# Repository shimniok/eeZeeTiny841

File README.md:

eeZeeTiny841 is a breakout / target board for breadboarding with the powerful ATtiny841.

[Click here for the User Guide](documentation/README.md)

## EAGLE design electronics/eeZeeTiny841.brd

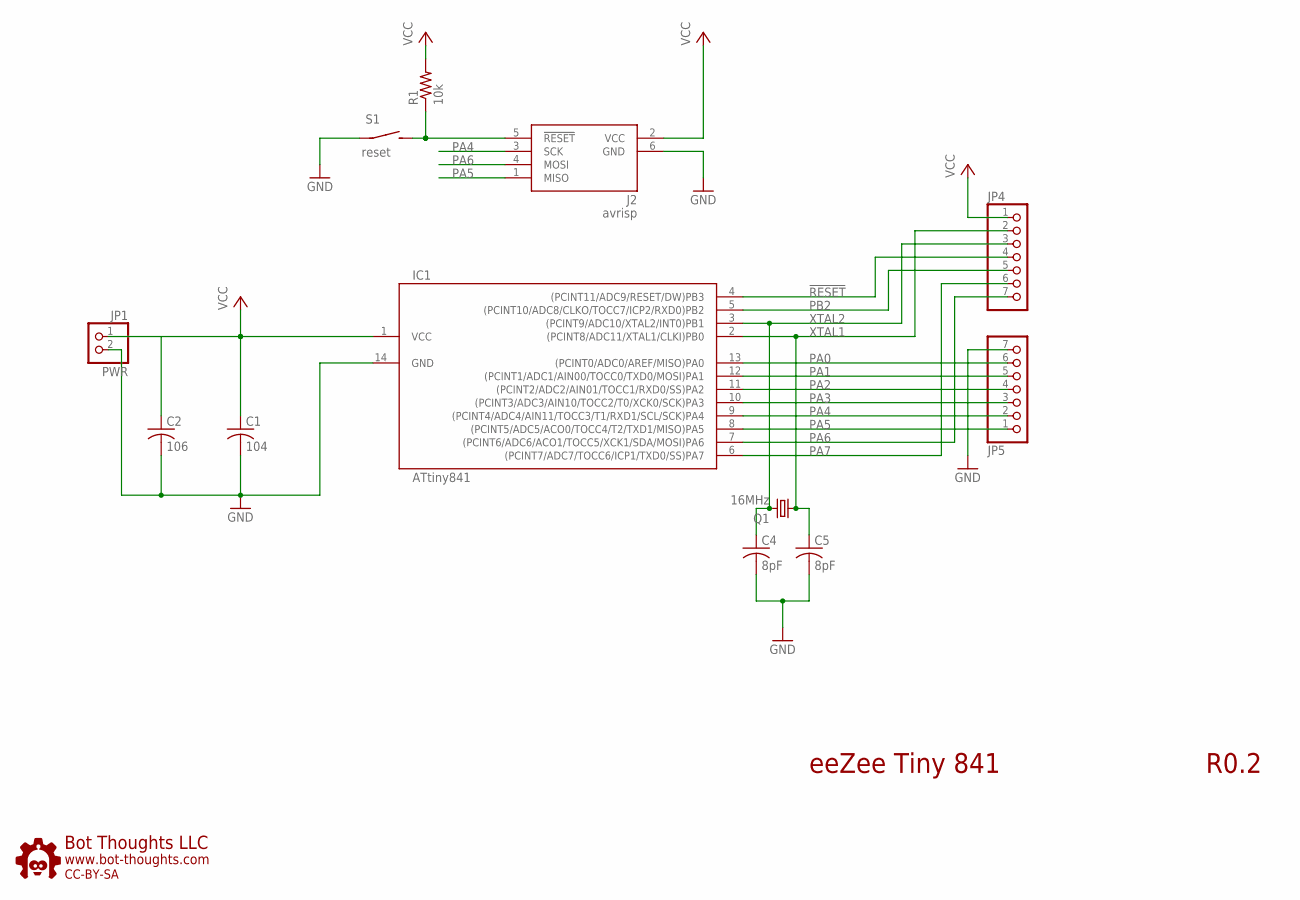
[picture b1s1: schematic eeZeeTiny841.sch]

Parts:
C1: 104; C0603; PARTNO 0603YC104KAT2A
C2: 106; C1206; PARTNO MCTT21X106M6R3CT
C4, C5: 8pF; C0603; PARTNO 0603YC104KAT2A
IC1: ATtiny841; 14SOICN
J2: avrisp; CON6P2R
JP1: PWR; 1X02-S
JP4, JP5: PINHD-1X07_2.54-S; 1X07-S
Q1: 16MHz; NDK_2PAD_5X3
R1: 10k; R0603; PARTNO ERJ-3GEYJ103V
S1: reset; 6MMTACTILE_RECT
U$1: BTLOGO-LOGO-MD; BTLOGOM

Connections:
!RESET: IC1.4 ((PCINT11/ADC9/RESET/DW)PB3), J2.5 (!RESET), JP4.4, R1.1, S1.P$2 (S)
GND: C1.2, C2.2, C4.2, C5.2, IC1.14 (GND), J2.6 (GND), JP1.2, JP5.7, S1.P$1
PA0: IC1.13 ((PCINT0/ADC0/AREF/MISO)PA0), JP5.6
PA1: IC1.12 ((PCINT1/ADC1/AIN00/TOCC0/TXD0/MOSI)PA1), JP5.5
PA2: IC1.11 ((PCINT2/ADC2/AIN01/TOCC1/RXD0/SS)PA2), JP5.4
PA3: IC1.10 ((PCINT3/ADC3/AIN10/TOCC2/T0/XCK0/SCK)PA3), JP5.3
PA4: IC1.9 ((PCINT4/ADC4/AIN11/TOCC3/T1/RXD1/SCL/SC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), J2.3 (SCK), JP5.2
PA5: IC1.8 ((PCINT5/ADC5/ACO0/TOCC4/T2/TXD1/MISO)PA5), J2.1 (MISO), JP5.1
PA6: IC1.7 ((PCINT6/ADC6/ACO1/TOCC5/XCK1/SDA/MOSI)P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), J2.4 (MOSI), JP4.7
PA7: IC1.6 ((PCINT7/ADC7/TOCC6/ICP1/TXD0/SS)PA7), JP4.6
PB2: IC1.5 ((PCINT10/ADC8/CLKO/TOCC7/ICP2/RXD0)PB2), JP4.5
VCC: C1.1, C2.1, IC1.1 (VCC), J2.2 (VCC), JP1.1, JP4.1, R1.2
XTAL1: C5.1, IC1.2 ((PCINT8/ADC11/XTAL1/CLKI)PB0), JP4.2, Q1.P$1 (1)
XTAL2: C4.1, IC1.3 ((PCINT9/ADC10/XTAL2/INT0)PB1), JP4.3, Q1.P$2 (2)

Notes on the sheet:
eeZee Tiny 841
R0.2

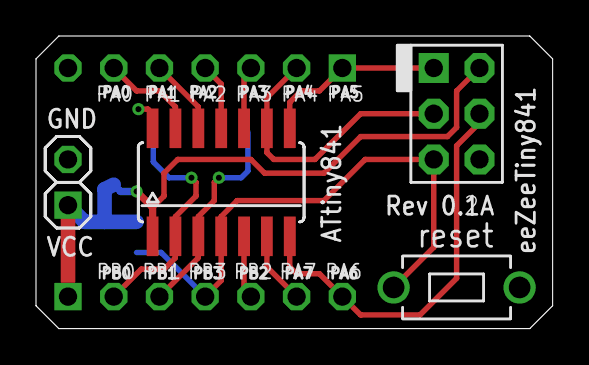
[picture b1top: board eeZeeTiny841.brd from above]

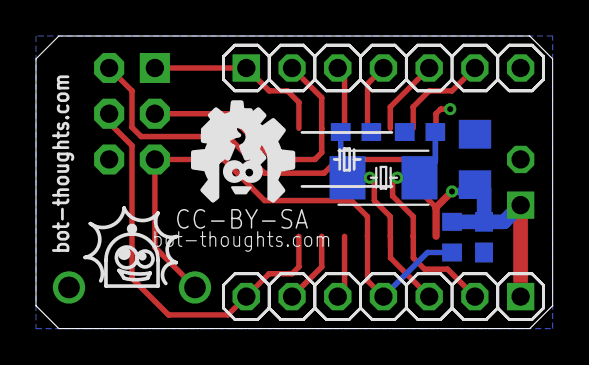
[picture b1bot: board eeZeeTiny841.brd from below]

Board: 2 copper layers, 28.7 x 16.3 mm, 13 parts (9 on the bottom side), 14 nets.

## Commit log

2014-01-22 Initial draft revision 0.1
2014-01-22 Fixing accidentally flipped schematic. D'oye!
2014-03-01 Example code for ATtiny841
2014-03-01 Minor mods to board/schematic. avrdude config from AVRfreaks forum.
2014-03-01 Renamed avrdude config
2014-03-01 Revised to use non-reset, non-xtal pins.
2014-03-01 Revised hierarchy with electronics subdir
2014-03-18 Subdirectory for multiple firmware examples
2014-03-18 Initial version, larson scanner type demo
2014-03-18 Fixed char / addition / subtraction bug, converted to larson type scanning, back and forth.
2014-03-18 Added hex files for easier testing
2014-10-17 Converted to 10mil/8mil spacing, changed PTHs to octagon.
2014-11-26 Added avrdude.conf content for ATtiny841, added README explaining how to set up.Z
2014-11-26 Modified readme to point to web-based help.
2015-04-24 Added delay in hopes of AVR Dragon having time to reset after install, fixed minor typos
2015-04-24 minor reformat. fixed loop variables. changed delay
2015-04-24 removed hex file
2015-05-01 added Makefile to larson scanner code
2015-05-05 Added LICENSE and README files
2015-06-10 Added wiki page in documentation
2015-06-10 renamed main wiki to README.md
2015-09-04 Formatting on Makefile
2015-11-17 Updated to current user guie format. Included additional soldering pics and instructions. Converted some images to local.
2015-11-17 Added local images
2015-11-17 removed unnecessary avrisp pinout
2015-11-17 renamed firmware to examples
2015-11-17 Added more local images, removed links to source, etc.
2015-11-17 removed hex link
2015-11-18 added assembly pictures
2016-02-11 fixed makefile fuse formatting, provided option for external clock
2016-02-11 fixed problem with comment on LFUSE
2016-02-12 reverted to internal 8mhz
2016-02-12 added fuses, minor reformatting
2016-02-25 added makefile for setting fuses conveniently for xtal vs. no onboard xtal.
2016-02-25 added Arduino larsen example
2016-02-25 updated pinout with arduino pins, added source xcf
2016-02-25 updated user guide, reorganized arduino vs. gcc, modified pinout image size for ISP
2016-02-26 Fixed EFUSE configuration. c.f. http://www.avrfreaks.net/comment/1111736#comment-1111736
2016-03-16 revised layout, updated logo
2016-03-16 updated gerbers, zip
2017-05-17 Created file for adding AVR Dragon to arduino
2017-05-17 Added/updated instructions for avrdude.conf to recognize ATtiny841, and for adding AVR Dragon to Spence Konde's ATTinyCore package.
2017-05-17 Updated README.txt to README.md with correct reference to install instructions.
2017-05-17 Updated fuses, removed Wire reference
2017-06-26 Separated board assy instructions into separate file
2017-06-26 added user guide link
2017-06-26 removed extraneous text
2017-06-26 rewrite for clarity, added usbasp / atmel studio writeup
2017-06-26 updated examples link
2017-06-26 fixed links
2017-06-26 created subdirs for example code
2017-06-26 updated for other programmer
2017-06-26 moved examples link
2017-06-26 added dragon info, minor tweaks
2017-06-27 added supported chips
2017-06-27 added avrdude examples bullet
2019-06-05 added and enabled usbasp programmer

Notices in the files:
electronics/eeZeeTiny841.brd:
CC-BY-SA
